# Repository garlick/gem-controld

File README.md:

### gem-controld

This project is a control system for a german equatorial telescope mount.
The mount is a Parallax series 125 head that has been retrofitted
with stepper motors on RA and DEC axes.

Electronics are based on the Beaglebone Black ARM-based single board
computer running Linux, a custom interface "cape" with two
[RS-422 transceivers](http://www.ti.com/product/sn65hvd379) which connect to
[Schneider Electric IM483i](http://motion.schneider-electric.com/downloads/manuals/im483i_ie.pdf) motion controllers, and GPIO based
[autogider](http://www.store.shoestringastronomy.com/guide_port_cables.pdf) and
[handbox](http://www.bbastrodesigns.com/handpad-assembly_notes.html) interfaces.
The electronics are packaged in a 7x7x5 DIN rail enclosure that mounts to
the telescope pier.

Software is based on reactive (event-driven) programming, with the goal
of keeping complexity down and separation of concerns among modules up.

### status

The handbox can be used to slew the telescope in two speeds, and the RA axis
tracks at a fixed sidereal rate.

The Meade LX200 and Tangent BBOX protocols can be used to sync the telescope
with a starmap program like Sky Safari, or control it (LX200 only).  A simple
pointing model is implemented with a one-star alignment available through
the remote application.

Autoguiding on an ST-4 interface works.

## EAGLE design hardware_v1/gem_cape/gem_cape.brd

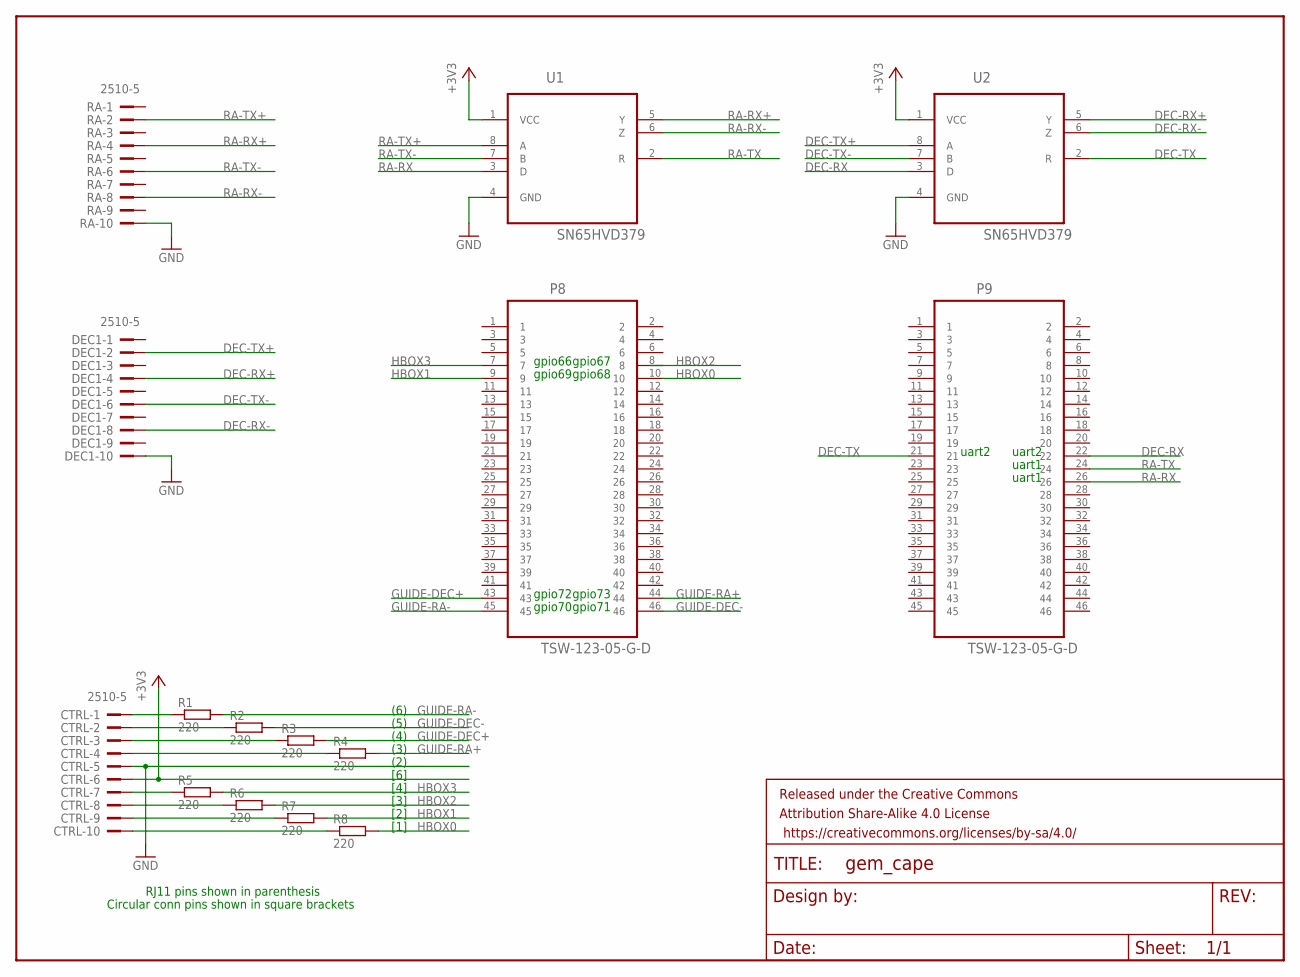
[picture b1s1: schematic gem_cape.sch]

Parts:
CTRL: 2510-5; PAK100/2500-5-10
DEC1: 2510-5; PAK100/2500-5-10
FRAME1: FRAME-LETTER; CREATIVE_COMMONS
P8, P9: TSW-123-05-G-D; SAMTEC_TSW-123-05-G-D
R1, R2, R3, R4, R5, R6, R7, R8: 220; R0805
RA: 2510-5; PAK100/2500-5-10
U1, U2: SN65HVD379; SOIC127P600X175-8N; MPN SN65HVD379

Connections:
+3V3: CTRL.6, U1.1 (VCC), U2.1 (VCC)
DEC-RX: P9.22, U2.3 (D)
DEC-RX+: DEC1.4, U2.5 (Y)
DEC-RX-: DEC1.8, U2.6 (Z)
DEC-TX: P9.21, U2.2 (R)
DEC-TX+: DEC1.2, U2.8 (A)
DEC-TX-: DEC1.6, U2.7 (B)
GND: CTRL.5, DEC1.10, RA.10, U1.4 (GND), U2.4 (GND)
GUIDE-DEC+: P8.43, R3.2
GUIDE-DEC-: P8.46, R2.2
GUIDE-RA+: P8.44, R4.2
GUIDE-RA-: P8.45, R1.2
HBOX0: P8.10, R8.2
HBOX1: P8.9, R7.2
HBOX2: P8.8, R6.2
HBOX3: P8.7, R5.2
unnamed: CTRL.1, R1.1
unnamed: CTRL.2, R2.1
unnamed: CTRL.3, R3.1
unnamed: CTRL.4, R4.1
unnamed: CTRL.7, R5.1
unnamed: CTRL.8, R6.1
unnamed: CTRL.9, R7.1
unnamed: CTRL.10, R8.1
RA-RX: P9.26, U1.3 (D)
RA-RX+: RA.4, U1.5 (Y)
RA-RX-: RA.8, U1.6 (Z)
RA-TX: P9.24, U1.2 (R)
RA-TX+: RA.2, U1.8 (A)
RA-TX-: RA.6, U1.7 (B)

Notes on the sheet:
(6)
(5)
(4)
(3)
(2)
[6]
[4]
[3]
[2]
[1]
RJ11 pins shown in parenthesis
Circular conn pins shown in square brackets
uart2
uart1
gpio68
gpio69
gpio67
gpio66
gpio72
gpio71
gpio73
gpio70

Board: 2 copper layers, 16 parts (2 on the bottom side), 30 nets, no tracks yet.

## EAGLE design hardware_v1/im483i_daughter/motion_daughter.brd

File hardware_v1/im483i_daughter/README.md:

### IM483i daughter board for GEM

This is a daughter board for the Intelligent Motion Systems, Inc
IM483i minature high performance microstepping module.  It breaks
out the RS-422 and hand controller inputs, and ties some outputs to
LED's mounted on the board.

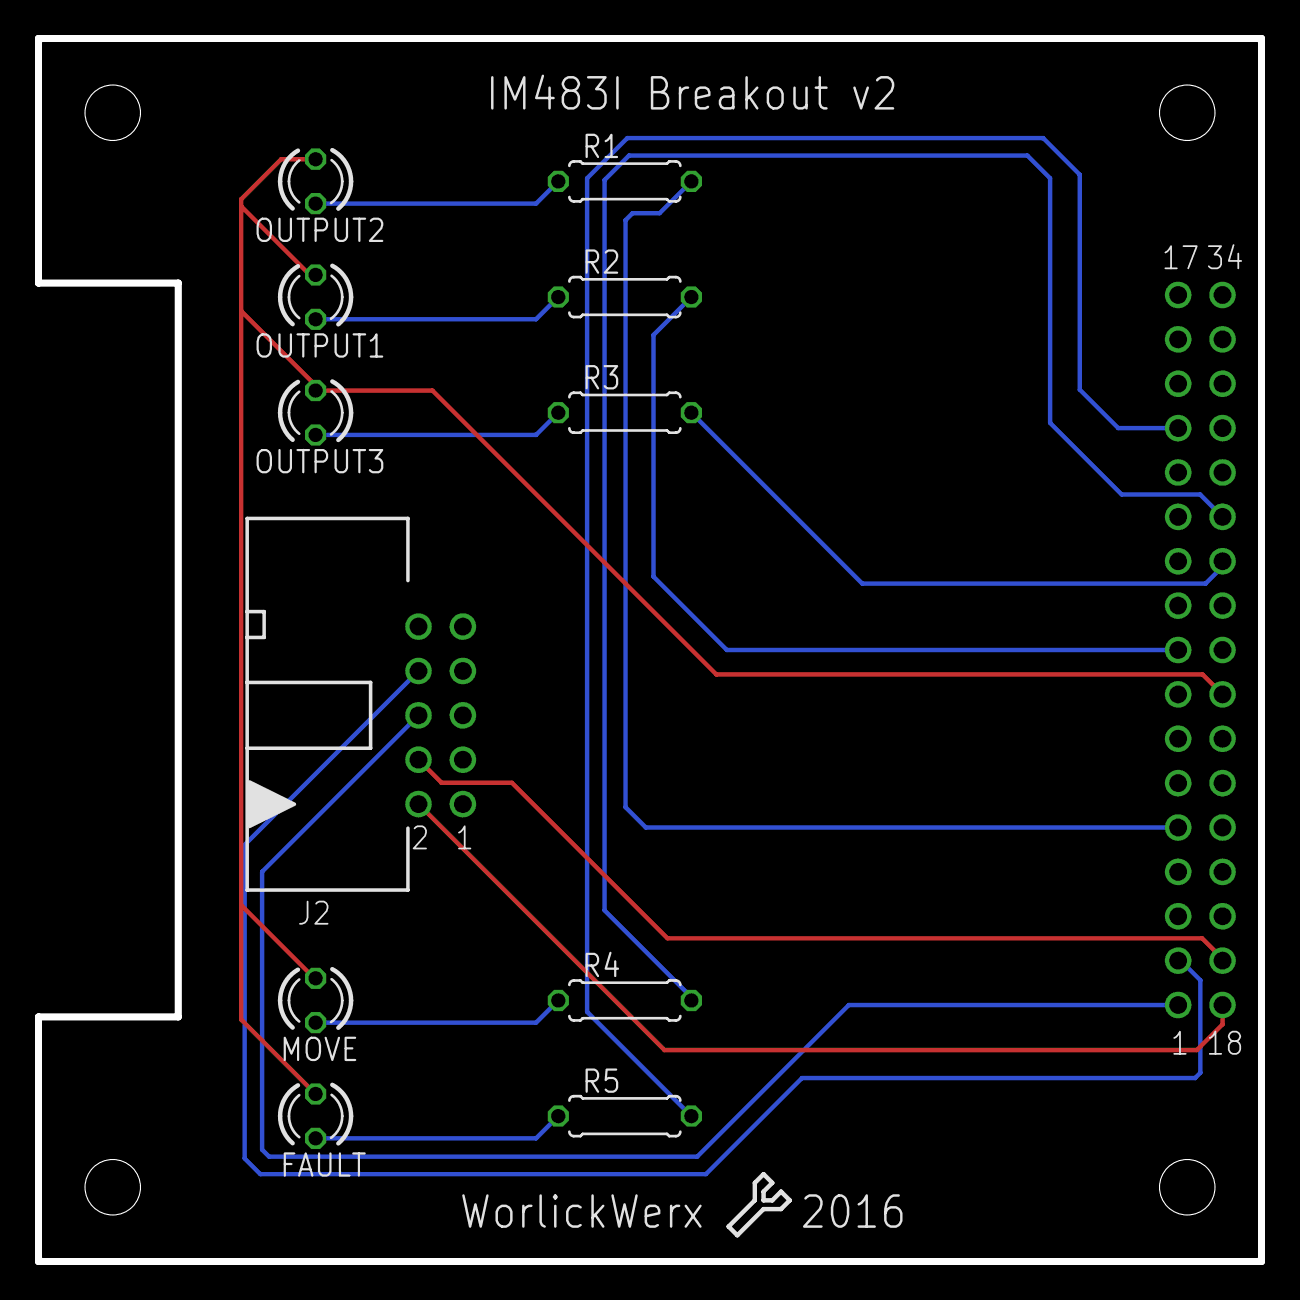
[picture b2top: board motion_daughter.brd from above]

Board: 2 copper layers, 70.0 x 70.0 mm, 12 parts (0 on the bottom side), 16 nets.

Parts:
FAULT: LED3MM
J1: WW-34P-SPECIALIM483I_HEADER; PAK100/2500-34
J2: WW-10P5; PAK100/2500-5-10
MOVE: LED3MM
OUTPUT1, OUTPUT2, OUTPUT3: LED3MM
R1, R3, R5: 970; 0207/7
R2, R4: 470; 0207/7

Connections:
FAULT: J1.P14, R5.2
GND: J1.P27, J2.10
MOVING: J1.P29, R4.2
unnamed: OUTPUT3.K, R3.1
unnamed: OUTPUT1.K, R2.1
unnamed: OUTPUT2.K, R1.1
unnamed: MOVE.K, R4.1
unnamed: FAULT.K, R5.1
OUTPUT1: J1.P9, R2.2
OUTPUT2: J1.P5, R1.2
OUTPUT3: J1.P28, R3.2
RX+: J1.P19, J2.4
RX-: J1.P2, J2.8
TX+: J1.P18, J2.2
TX-: J1.P1, J2.6
VCC: FAULT.A, J1.P25, MOVE.A, OUTPUT1.A, OUTPUT2.A, OUTPUT3.A

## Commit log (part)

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2015-02-04 get basic motion commands working
2015-02-22 add sample config file
2015-02-22 gpio: assign buttons to motion controls
    N, S, E, W set configurable slew velocities (fast/slow setting).
    M1+M2 exits the program, termination all motion.
    M1 displays position (X,Y)
2015-02-22 revise GPL headers for v2+
2015-03-01 gem: factor axis_init()
2015-03-01 make gpio bits configurable via config file
2015-03-01 gem: rework handpad interface with ev_loop
2015-03-02 add initial device tree overlay
2015-03-03 dts: complete but untested
2015-03-03 fix broken README.md links
2015-03-22 doc: minor editing
2015-03-22 config: fix libini usage
    Check parse_ini() return value and correctly display error for
    file open, out of memory, and parse error (with line number).
    Parser callbacks must return 0 only on failure.
2015-03-22 build: set $(prefix) in Makefile.inc
    Also don't hardwire the config prefix in gem.c.
    Derive it from $(prefix), defined on the command line.
2015-03-23 enable zeromq ROUTER socket for handling requests
    Bind to a configured ROUTER socket URI, then create a libev watcher
    to respond when a message arrives.
    Disable czmq's default signal handling, which caused systemd to get
    stuck when it tries to stop/restart gem-contrld.
2015-03-23 add remote position query
2015-03-23 add gem stop, track, go, zero commands
2015-03-23 add goto command, disable motion timeouts
    A goto command gets a response from the motion controller immediately.
    However, the next goto or track command will not be responded to
    until the first goto finishes. Thus (a) timeouts are inappropriate, and
    (b) with no timeouts, issuing the second command blocks the event loop,
    so it should be avoided if possible, e.g. by polling the position.
2015-03-23 fix attributes on source files
2015-03-23 libcommon: factor out configfile
    Both commands and the daemon need to parse the config file
    so move this to a place where both can conveniently link to it.
2015-03-24 don't allow motion until mount has been zeroed
    The handpad now has 'zero' and 'start/stop tracking' assigned
    to the two mode buttons. Allow handpad slewing but disable
    remote goto, park, or read position until the mount has been
    zeroed. It can be zeroed at the handpad or remotely.
    Also don't start initial tracking until requested (remotely or
    via the handpad). This is not because it is a danger so much
2015-03-24 Use arcsec/sec for tracking units
    Tracking op now accepts velocities in arcsec/sec and we calculate the
    appropriate controller velocity based on configured steps/rev, mode,
    and resolution.
    Remove the 'track' configuration, and instead calculate the sidereal
    tracking rate based on the above and a constant sidereal arcsec/sec.
2015-03-24 drop STEPS op as we are scaling on server side
    No need for a remote client to query this value as all interactions
    over the wire will be in standard units.
2015-03-25 motion: tolerate a soft start w/o losing origin
    Avoid doing a ^C reset in motion_init(), unless MOTION_RESET
    flag is present, as this resets the origin. Modify the
    motion_init() "initiate communications" sequence to be idempotent.
    Add motion_set_port(), motion_get_port() for general purpose GPIO
    access, and stop touching the green LED in motion_init().
    At startup, read the green LED state, and if set (off) for both
2015-03-25 don't stop motion when warm starting gem-controld
    motion_init() should not send a soft stop command. Add a 'coldstart'
    parameter to motion_init() so it can tell inform the caller whether
    the hello sequence detected an already running controller.
    Avoid initializing resolution, mode, current, etc. if coldstart returns
    false. At least one of these commands has the effect of stopping motion.
    Finally, initialize 'stopped' based on the actual motion status of
2015-03-25 rename gem-controld to gem-motiond
2015-03-25 account for t_axis direction reversal
    Set 'steps' negative for t_axis, then make sidereal constant positive.
    This way (t,d) has the same sign as (LHA,DEC).
2015-03-25 set d park position to 90 degrees in config file
2015-03-26 add gnuplot template for position viz
2015-03-26 return EAGAIN to GOTO/PARK when motion in progress
    Query the motion controllers to ensure they are not already
    carrying out a move before allowing a GOTO or PARK move to
    be queued, since this would stall the event loop.
2015-03-27 regularly publish position information
    Add a new zeromq pub/sub socket. Add a timer to motiond, and
    when it fires, publish the telescope position. When idle/tracking
    do this every 5s, but increase frequency when a move is in progress.
    Modify 'gem plot' so that it subscribes to these updates and
    passively waits for position updates, pushing them to the gnplot window
    at whatever frequency they are offered.
2015-06-30 dts: add focus axis
    Add a third axis for Focus, connected to /dev/ttyO4.
    Electrically all three axes are identical.
2015-07-02 motiond: add FLAG_F_TRACKING
    When handpad is controlling focus, motion controller may be in
    constant velocity state, as opposed to executing a move
    (FLAG_F_MOVING).
2015-07-02 add 'f' axis
    Add axis to config data structure so we can have an [f_axis] stanza
    in the config file.
    - define 'steps' to be steps per meter of focus travel
    (compare steps/rev for t, d axes)
    - define low_limit, high_limit to be in microns
    (compare arcsec to t, d axes)
2015-07-02 motiond/hpad: change mode key assignment
    Now M1+M2 sets the origin,
    M1 toggles focus mode
    M2 toggles stop
2015-08-31 guide: add initial guide port support
    Add guide pins to DTS file.
    Add [guide] stanza to config.ini and libcommon config parser,
    patterned after [hpad].
    Add guide class to motiond, patterned after hpad class.
    Configure the guide class in the gem-motiond and emit debugging
    printfs when state changes, if running in debug mode.
2016-07-23 dts: update uart indexing for Debian jessie
    Apparently uart numbering now maps one to one with
    the beaglebone documentation.
2017-09-16 hardware_v1: change resistor values, add pdfs
2017-09-17 src: consolidate project source
2017-09-17 src/guide: eliminate useless typedefs
2017-09-17 src/configfile: eliminate useless typedefs
2017-09-18 dts: drop focus uart, change hbox mode
    Drop the uart for deprecated focus axis.
    Change the hbox pin modes from 0x2f to 0x27,
    which enables internal pull-down resistors.
    This reflects a change in the prototype
    where the external pulldown resistors were
    removed.
2017-09-18 src/test-hpad: add test for hpad/guide
2017-09-18 src/motion: document LED bits on motion control
2017-09-18 README.md: link to dts/README.md
2017-09-18 dts/README.md: tidy up
2017-09-18 dts/README.md: drop info now in top level README.md
2017-09-18 README.md: fix typo
2017-09-18 src/daemon: incorporate bbox support
2017-09-18 src/daemon: rename --debug to --debug-motion
2017-09-18 src/daemon: add --debug-hpad
2017-09-18 README.md: update status
2017-09-19 daemon: add --west option
    The RA motor runs with a positive tracking velocity when
    the telescope is on the east side of the pier, observing
    west of the meridian. It runs with a negative velocity
    when tracking with the telescope on the west side of the
    pier, observing east of the meridian.
    Make the default be "observing east", and add a --west
2017-09-19 daemon: drop M1+M2 "zero" action
    Drop the M1+M2 hpad action to zero the motion controllers
    at the current position as this is not used.
2017-09-19 bbox: limit debug verbosity
    Drop some debug output that wasn't all that useful.
2017-09-20 lx200: add lx200 protocol support
    Implement enough of the LX200 command so that Sky Safari
    can connect, including setting date and location.
2017-09-22 lx200: wire in util module
    Hook the lx200 protocol into the util module, so now the
    telescope can be aligned and report its position.
2017-09-24 lx200: drop unnecessary list of commands from top
2017-09-24 point: add point_get_target() for goto
2017-09-24 daemon: enable lx200 goto
2017-09-24 daemon: change velocities to degrees/sec
    Change config and internal speeds from arcsec/sec to degrees/sec,
    to be consistent with positional units where degrees are used.
    Also change the units for "speed" settings in the config file.
2017-09-24 daemon: map hpad M1 key to emergency stop
    Problem: need a way to manually stop the telescope if
    things go wrong.
    Pressing M1 executes a "soft stop" (with deceleration) on
    both axes.
2017-09-24 config: add "medium" slew rate
    Configure a medium slew speed and have the hpad
    select between medium and fast slew rates with its
    two-way switch.
2017-09-26 guide: use common slew parameters
2017-09-26 hpad: use common slew parameters
    Modify hpad module ot use common slew bits, and also
    split out control (M1 + M2) keys and velocity.
    Refactor "slew event" handling code in daemon.c so that the
    slew start/stop logic is in one place. It should now be possible
    to simultaneously slew both axes without terminating one axis
    when the button for the other is released. (While the hpad
2017-09-30 motion: rename motion_get_io(), motion_set_io()
    Rename motion_get_port() and motion_set_port() to
    motion_get_io() and motion_set_io(), and create an
    enum for bit values using their names from the IM
    programming manual.
2017-09-30 motion: rename motion_goto_absolute(), _relative()
2017-09-30 motion: rename motion_soft_stop()
2017-09-30 motion: switch to reactive model
    Switch to reactive programming model internally.
    Drop code to detect whether motion controllers
    have been previously initialized, and instead
    unconditionally perform a software reset and
    load configuration parameters. RA tracking is
    always disabled on startup.
2017-10-07 motion: hide axis velocity calculation
    Add 'ccw' (step direction reversal) and 'steps' (number
    of steps per revolution) to the motion configuration, and
    then allow slew/tracking velocity to be set in degrees per
    second, thus hiding some im483i specific code in the motion
    module where it belongs.
2017-10-07 daemon: if --west, flip DEC not RA (!)
    Of course after a meridian flip, it is the DEC axis that must
    be reversed, not RA. The RA axis is not reoriented so it still
    must track the earth's rotation in the same direction! Duh.
2017-10-07 daemon: reverse RA tracking direction
    In the last PR, I manage to set RA tracking the wrong
    direction. Reverse.
2017-10-07 motion: [cleanup] define MAX_CMD and MAX_BUF
2017-10-07 motion: make simple commands synchronous
    Tighten up the im483i protocol parsing a bit by forcing
    simple commands to wait for an echo response indicating they
    have been processed. This ensures any unexpected response or
    timeout is associated wtih the offending command in error messages.
    Not much was probably gained by the "fire and forget" approach
    being used, where the next command has to wait if the previous
2017-10-07 lx200, point: split set_position() into ha, dec
    Problem: For every SkySafari/LX200 request for position,
    the motion controllers receive two requests.
    lx200 protocol splits position request into separate
    RA and DEC requests. Since our motion, point, and lx200 callbacks
    are not split, this requires each single-axis fetch to do the
    work for both axes.
2017-10-07 daemon: allow +-120&* of motion instead of +-90*
    Problem: if mount is powered up (zeroed) pointing at polaris,
    the dec axis may need to slew beyond 90 degrees to cover one half
    the visible sky.
    Change the limit to +-120*.
2017-10-25 point: add point_get_latitutde, _longitude
2017-10-25 point: add get_gmtoff, _localtime, _localdate
    Add functions for retrieving the local time/date/gmt offset,
    derived from the system time.
2017-10-25 point: add note about longitude
2017-10-26 daemon: call lx200_set_tracking_rate() when asked
2017-10-28 test-lx200: add missing callbacks

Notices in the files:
parts and their libraries:
SparkFun-Aesthetics: Licensing: Creative Commons ShareAlike 4.0 International - https://creativecommons.org/licenses/by-sa/4.0
SparkFun-Aesthetics: Released under the Creative Commons Attribution Share-Alike 4.0 License
SparkFun-Aesthetics: https://creativecommons.org/licenses/by-sa/4.0
